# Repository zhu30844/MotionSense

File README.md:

# MotionSense

English | [简体中文](README_cn.md)

Last edited: 2026-11-27

> **Status.** To use MotionSense, take a
> [v1 release](https://github.com/zhu30844/MotionSense/releases) or the
> [`1.x` branch](https://github.com/zhu30844/MotionSense/tree/1.x). `main` is
> being reworked towards 2.0, and nothing on it is promised to work until 2.0
> is released.

Motion-triggered video recording for the Luckfox Pico Pro Max (Rockchip
RV1106; the Pico Ultra is planned for after 2.0). Records H.264 to HLS on
the SD card, serves a live view over WebRTC and a playback UI over HTTP, and
logs motion events to SQLite.

## What it is for

Originally written for a shared fridge — who took what. It may suit other
scenes of the same shape, static for hours with a few seconds of activity: a
dorm room, a store cupboard, a warehouse aisle, a basement.

- **Get through a whole day fast.** Idle stretches play back sped up, with no
  scrubbing back and forth.
- **See the moment at full speed.** Motion is recorded and played at the high
  rate.
- **Save storage.** Idle time is recorded at one frame per second, so a day of
  footage stays small.
- **See where the activity was.** Every switch to the high rate leaves a mark
  on the seek bar.

## Screenshots

Live view, with the OSD timestamp and the device status bar:

History: a calendar of the days with footage, coloured by how much motion each
day had:

Playback of one day. The red marks on the seek bar are the switches to the
high rate:

## Features

- **Adaptive frame rate.** Records at 1 fps while idle and about 30 fps while motion
  is detected. Thresholds, sensitivity and night mode are configurable.
- **HLS recording.** One `.ts` per keyframe by default, organised into
  date-based directories with a per-day event database and automatic cleanup
  when free space runs low.
- **Live view and playback.** Live H.264 over WebRTC, recordings
  browsable by date, plus a `/api/status` endpoint reporting uptime, memory,
  load, SoC temperature and the last day with footage.
- **OSD timestamp** burned into both the recording and the live stream.

## Requirements

- Luckfox Pico Pro Max, SPI NAND boot
- An SD card, **ext4**. It must not carry the `orphan_file` feature — the 5.10
  kernel cannot mount that read-write. See
  [docs/BUILD.md](docs/BUILD.md#the-sd-card).
- Enough card for the footage you want to keep. Below
  `storage.disk_free_min_mb`, 2 GB by default, the oldest day is deleted to
  make room; recording itself never stops.
- x86-64 Linux host

## Usage

1. **Flash the image.** Download the latest image and flash it to the onboard
   SPI NAND with the full one-click flash, not to the SD card. The Luckfox wiki
   covers how: [Getting Started](https://wiki.luckfox.com/Luckfox-Pico-RV1106/Getting-Started/Pico-Pro-Max/).
2. **Format the SD card as ext4.** On Windows, [DiskGenius](https://www.diskgenius.com/)
   can do it; on Linux, use the commands below.

   Check the version first with `mke2fs -V`. On 1.47 or later, run them as
   they are. Below 1.47 (Ubuntu 22.04 ships 1.46.5), drop `-O ^orphan_file`
   from step 4 of the commands, or it fails with `Invalid filesystem option
   set`; older versions never enable the feature anyway.

   ```bash
   # 1. Find the card first; do not pick the wrong disk
   lsblk -o NAME,SIZE,MODEL,MOUNTPOINTS

   # 2. Unmount any mounted partitions on the card
   sudo umount /dev/sdX?*

   # 3. Repartition: MBR, one partition across the whole card
   sudo parted -s /dev/sdX mklabel msdos mkpart primary ext4 1MiB 100%

   # 4. Format as ext4 without orphan_file
   sudo mkfs.ext4 -O ^orphan_file -m 0 -L MOTIONSENSE /dev/sdX1

   # 5. Check: orphan_file must not be in the output
   sudo dumpe2fs -h /dev/sdX1 | grep -i features
   ```

3. **Power up.** Insert the SD card and the camera, connect the network and
   power the board. It starts recording on boot with nothing to configure.
4. **Open the web page.** Browse to `http://<board IP>/` for the live view and
   playback. The address depends on how the board is connected:
   - **Ethernet to a router**: the board gets its address over DHCP. Find it in
     the router's device list, or with `adb shell ifconfig eth0`.
   - **USB to a computer**: the board's USB network interface is fixed at
     `172.32.0.93`, and the board gives the computer an address on the new
     interface that appears there. Open `http://172.32.0.93/`.
   - **Ethernet straight to a computer**: nothing hands out addresses, so both
     ends need one set by hand. See [Offline communication](https://wiki.luckfox.com/Luckfox-Pico-RV1106/Ethernet-Config/#1-offline-communication)
     on the Luckfox wiki.

## How it fits together

Two processes, split by what each language is good at:

- **`MotionSense`**, in C, owns the pipeline — ISP, encoder and IVS motion
  detection through Rockchip's rockit, writing HLS and the metadata databases
  to the card. Nothing sits between it and the hardware.
- **`motionsense-agent`**, in Go, owns the network — HTTP, the UI, the API. It
  never touches rockit, so **no cgo**: a static binary built with
  `CGO_ENABLED=0`, reading the databases through `modernc.org/sqlite` in pure
  Go. It serves on port 80 as root, 3000 otherwise.

They talk over a unix socket (`/tmp/motionsense-stream.sock`), which keeps the
split honest: the daemon can die without taking the web interface with it, and
the agent restarts without disturbing a recording.

Configuration is one `config.json` on the SD card. The daemon writes it with
the defaults on first boot and never overwrites it after that, so a blank card
still records. [docs/BUILD.md](docs/BUILD.md#configuration) lists the keys.

`S99motionsense` starts both; the vendor's `rkipc` app is not in the image. Each waits for the card to mount by itself, and is started again if it
exits; a recorder that stops storing frames resets the board through the
hardware watchdog. [docs/BUILD.md](docs/BUILD.md#supervision) has the
details. The script ships in the
image, so a flashed board records from first boot with nothing to install and
nothing to configure.

## Building

This is an application inside the Luckfox SDK, integrated the Rockchip SDK way
at `project/app/motionsense`. The SDK fork below carries the board
configuration, the device tree and the development environment; clone the
whole SDK:

**<https://github.com/zhu30844/luckfox-pico-sdk>**

```bash
git clone --recurse-submodules git@github.com:zhu30844/luckfox-pico-sdk.git
cd luckfox-pico-sdk
./build.sh lunch     # hardware "custom" -> MotionSense_Pro_Max
./build.sh
adb reboot loader                       # put the board in maskrom/loader mode
./rkflash.sh update
```

### Development container

The devcontainer is in the **SDK fork**, not in this repository — open
`luckfox-pico-sdk` in VS Code, not `MotionSense`. VS Code will offer *Reopen in
Container*; the image carries the cross toolchain, Go, and the build
dependencies, with `LF_SDK`, `LF_TOOLCHAIN` and `LF_SYSROOT` already set.

Editing this app means editing `project/app/motionsense` inside that workspace.
Building on the host works too — `./build.sh` puts the toolchain on `PATH`
itself — provided the SDK's build dependencies are installed.

[docs/BUILD.md](docs/BUILD.md) covers the build chain, the board configuration, the
on-device layout and what to check when something does not come up.
[docs/DEVNOTES.md](docs/DEVNOTES.md) covers working on the board: how to connect to it,
what to do when a link drops, and the bugs that present as something else.

## Known issues

- Switching between views raises the client count. Above about five clients
  the agent stops responding for a while.
- Motion has no hold window: the frame rate returns to 1 fps as soon as a
  still frame is reported. Events are typically under a second, so the end of
  an action can be recorded at the idle rate.
- Daylight saving is not honoured. Only the standard-time half of `/etc/TZ` is
  read, so a zone with DST is an hour out for half the year.

## Planned

See the [roadmap](docs/ROADMAP.md).

## Scope

A learning project. Not built, tested or reviewed as a security product, and
not suitable for one.

Concretely, on the image this repository produces:

- The HTTP interface has no authentication. Anyone who can reach port 80 can
  watch the live stream and every recording.
- The root password is the default, `luckfox`.
- Recordings and the metadata databases are unencrypted on the SD card.
- Nothing here has had a security review.

Use it only on a LAN you control. Do not expose it to the internet.

The author accepts no responsibility.

## Licence

MIT — see [LICENSE](LICENSE). [docs/THIRD-PARTY.md](docs/THIRD-PARTY.md) lists everything
in the tree that is not covered by it.

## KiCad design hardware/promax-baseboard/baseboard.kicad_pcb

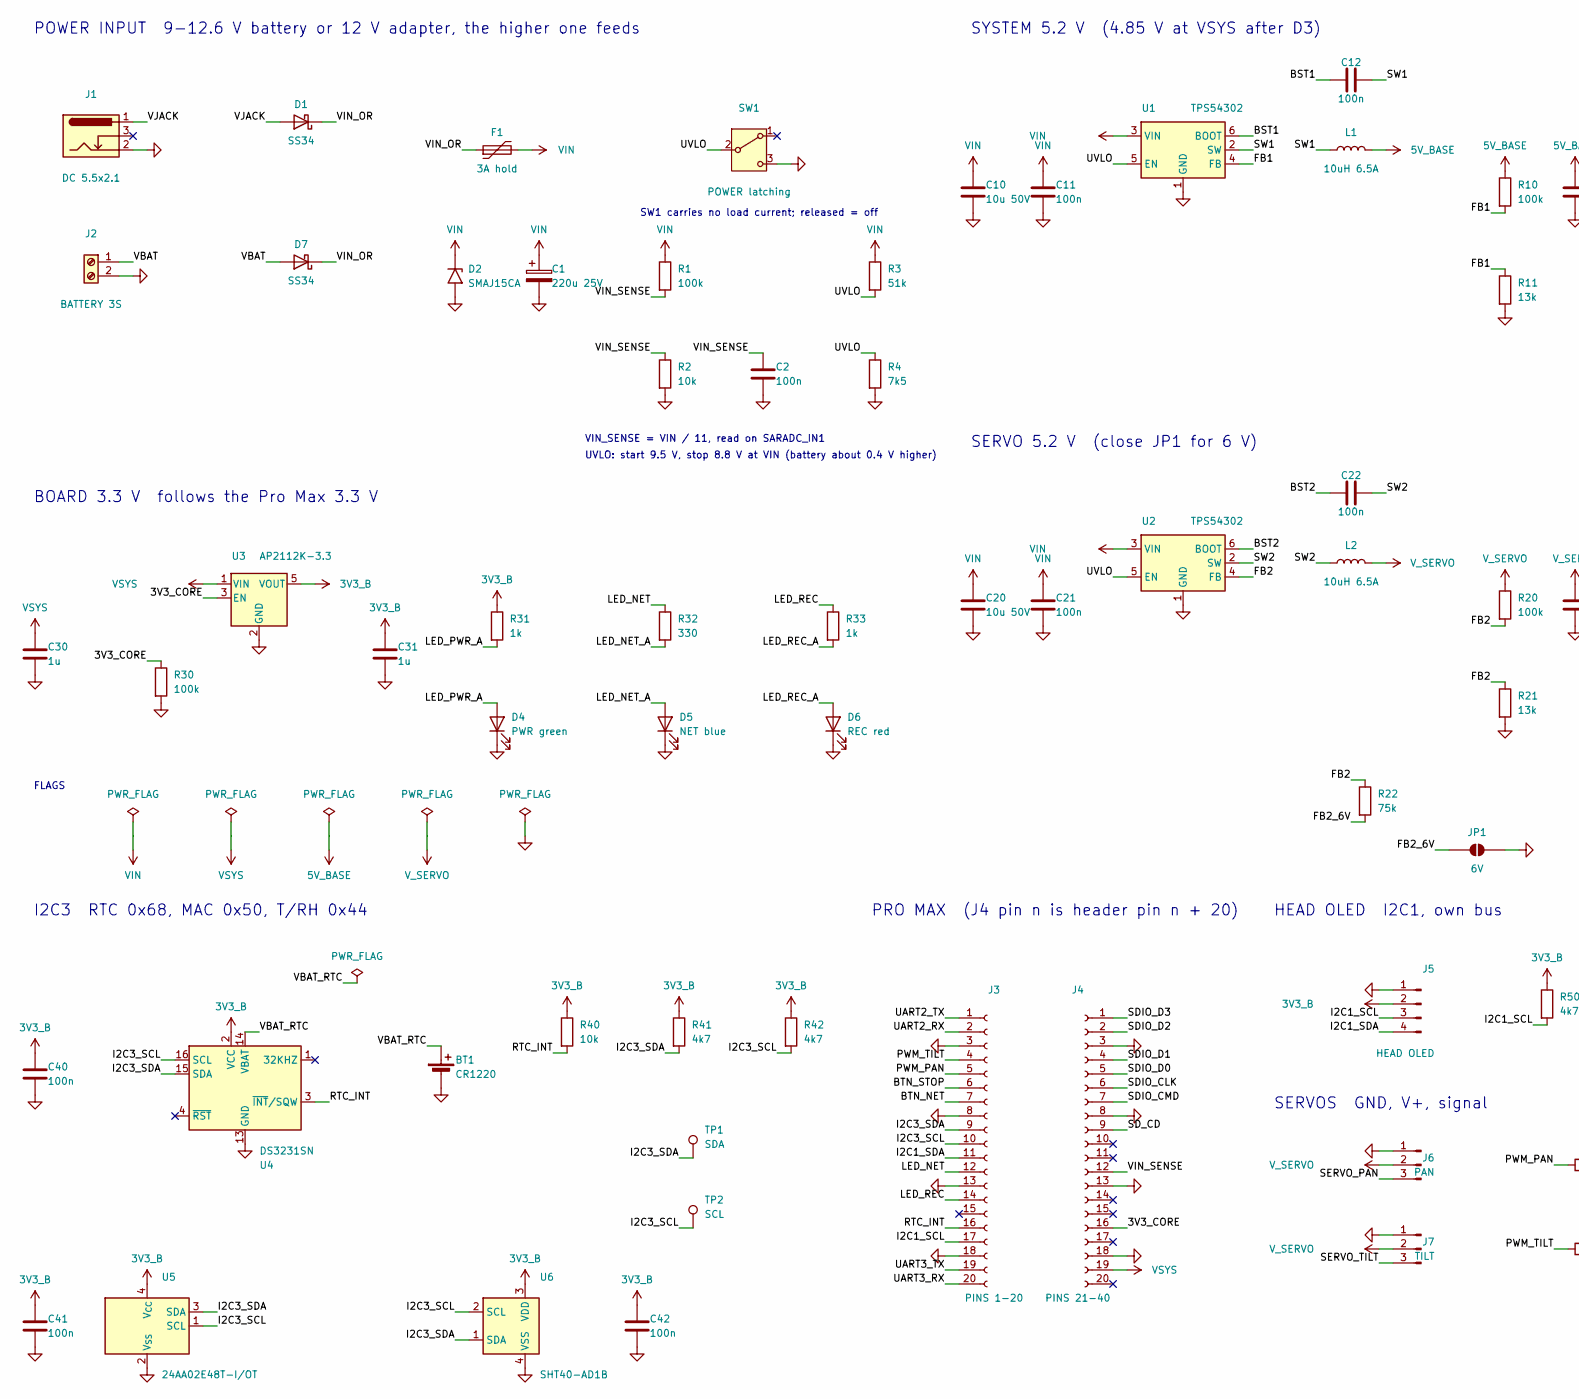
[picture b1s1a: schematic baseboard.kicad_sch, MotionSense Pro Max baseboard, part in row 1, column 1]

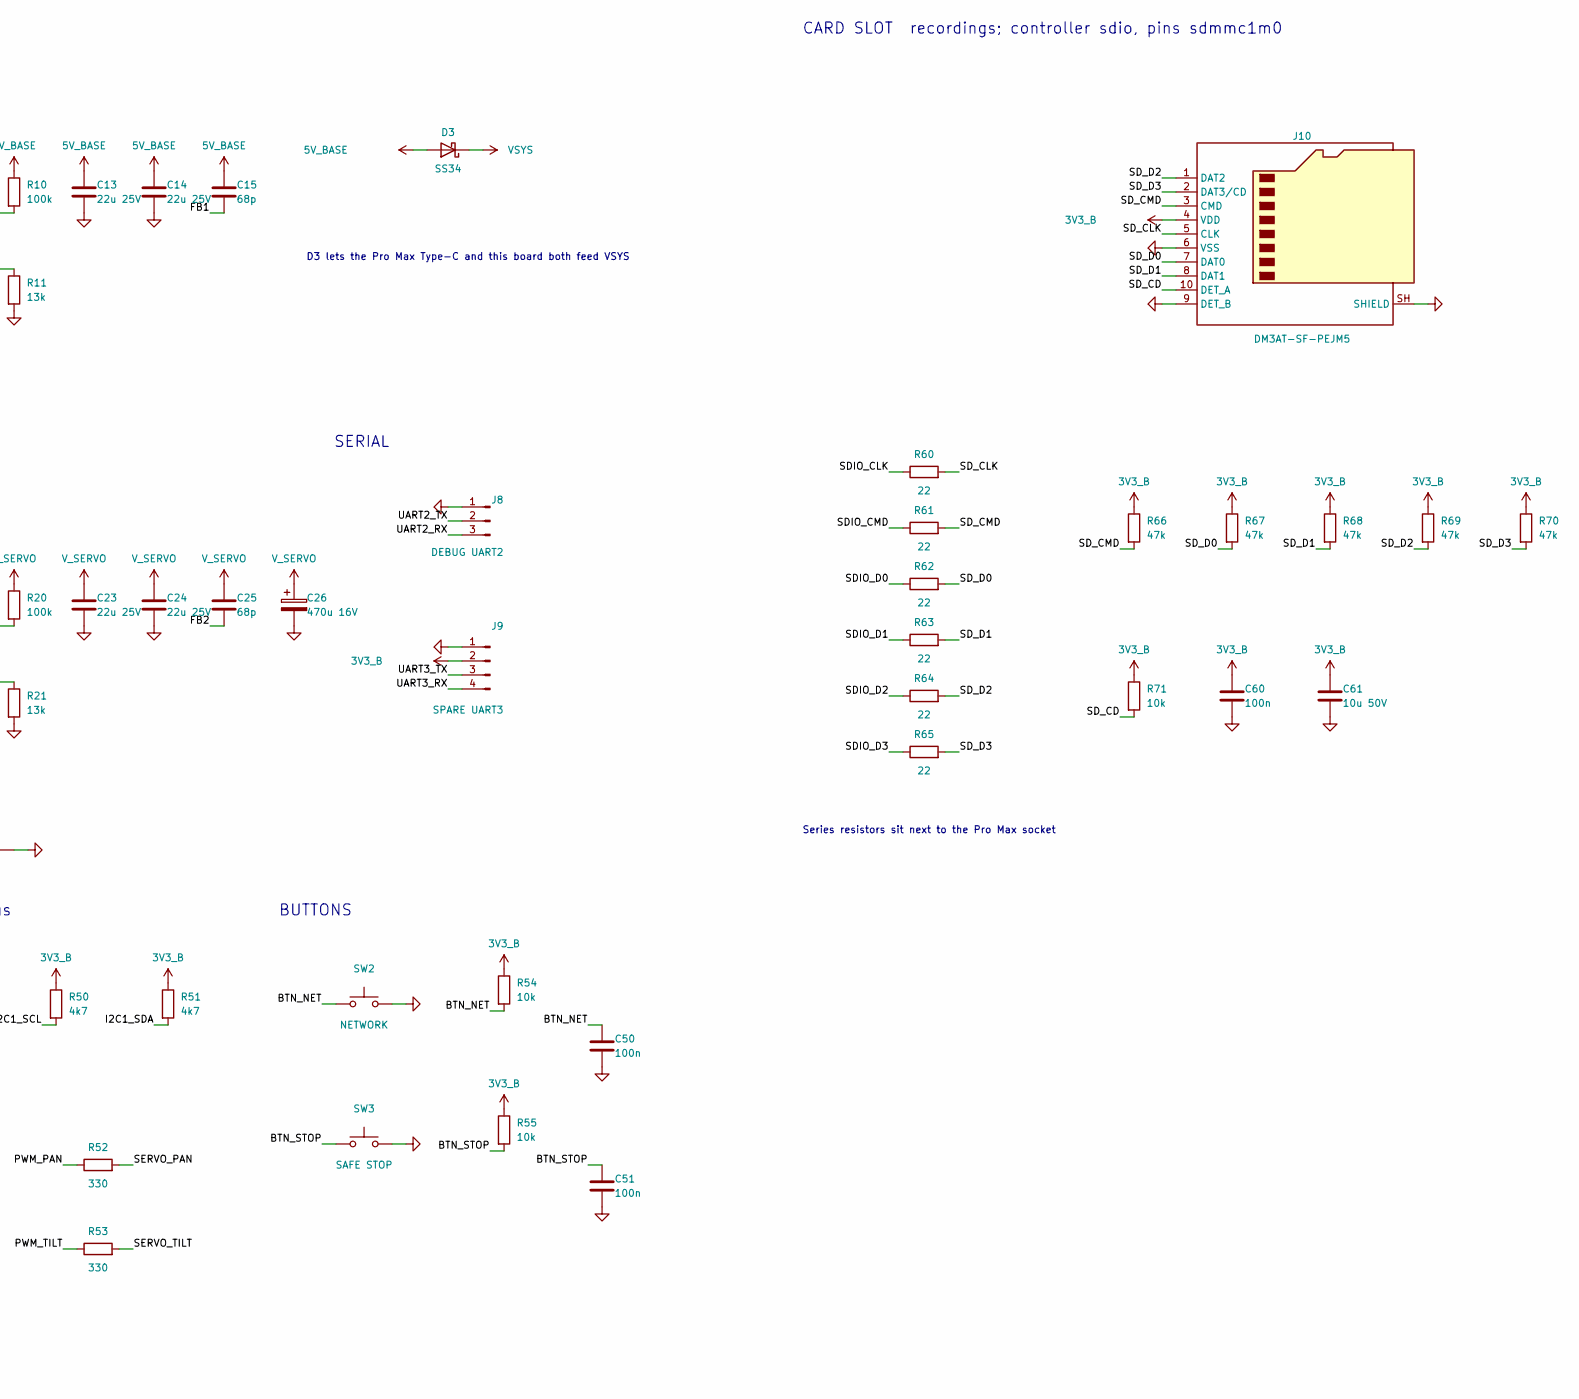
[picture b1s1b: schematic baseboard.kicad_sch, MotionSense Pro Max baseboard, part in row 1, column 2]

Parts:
BT1: CR1220; BAT-SMD_BS-12-B3AA011; LCSC C964723
C1: 220u 25V; CP_Elec_6.3x7.7; LCSC C2983317
C2, C11, C12, C21, C22, C40, C41, C42, C50, C51, C60: 100n; C_0805_2012Metric_Pad1.18x1.45mm_HandSolder; LCSC C49678
C10, C20, C61: 10u 50V; C_1206_3216Metric_Pad1.33x1.80mm_HandSolder; LCSC C13585
C13, C14, C23, C24: 22u 25V; C_1206_3216Metric_Pad1.33x1.80mm_HandSolder; LCSC C12891
C15, C25: 68p; C_0805_2012Metric_Pad1.18x1.45mm_HandSolder; LCSC C2171219
C26: 470u 16V; CP_Elec_6.3x7.7; LCSC C2977552
C30, C31: 1u; C_0805_2012Metric_Pad1.18x1.45mm_HandSolder; LCSC C28323
D1, D3, D7: SS34; D_SMA; LCSC C8678
D2: SMAJ15CA; D_SMA; LCSC C110044
D4: PWR green; LED_D3.0mm_Horizontal_O1.27mm_Z2.0mm; LCSC C181864
D5: NET blue; LED_D3.0mm_Horizontal_O1.27mm_Z2.0mm; LCSC C417350
D6: REC red; LED_D3.0mm_Horizontal_O1.27mm_Z2.0mm; LCSC C99771
F1: 3A hold; Fuse_1812_4532Metric_Pad1.30x3.40mm_HandSolder; LCSC C7500481
J1: DC 5.5x2.1; DC-IN-TH_DC-005-5.5-2.0; LCSC C16214
J2: BATTERY 3S; CONN-TH_P5.00_KF301-5.0-2P; LCSC C474881
J3: PINS 1-20; HDR-TH_20P-P2.54-V-F-2; LCSC C2905423
J4: PINS 21-40; HDR-TH_20P-P2.54-V-F-2; LCSC C2905423
J5: HEAD OLED; CONN-TH_B4B-XH-A-LF-SN; LCSC C144395
J6: PAN; PinHeader_1x03_P2.54mm_Vertical; LCSC C2937625
J7: TILT; PinHeader_1x03_P2.54mm_Vertical; LCSC C2937625
J8: DEBUG UART2; PinHeader_1x03_P2.54mm_Vertical; LCSC C2937625
J9: SPARE UART3; PinHeader_1x04_P2.54mm_Vertical; LCSC C2691448
J10: DM3AT-SF-PEJM5; microSD_HC_Hirose_DM3AT-SF-PEJM5; LCSC C114218
JP1: 6V; SolderJumper-2_P1.3mm_Open_RoundedPad1.0x1.5mm
L1, L2: 10uH 6.5A; IND-SMD_L7.5-W6.6_GSM0650; LCSC C51933843
R1, R10, R20, R30: 100k; R_0805_2012Metric_Pad1.20x1.40mm_HandSolder; LCSC C149504
R2, R40, R54, R55, R71: 10k; R_0805_2012Metric_Pad1.20x1.40mm_HandSolder; LCSC C17414
R3: 51k; R_0805_2012Metric_Pad1.20x1.40mm_HandSolder; LCSC C17737
R4: 7k5; R_0805_2012Metric_Pad1.20x1.40mm_HandSolder; LCSC C17807
R11, R21: 13k; R_0805_2012Metric_Pad1.20x1.40mm_HandSolder; LCSC C17455
R22: 75k; R_0805_2012Metric_Pad1.20x1.40mm_HandSolder; LCSC C17819
R31, R33: 1k; R_0805_2012Metric_Pad1.20x1.40mm_HandSolder; LCSC C17513
R32, R52, R53: 330; R_0805_2012Metric_Pad1.20x1.40mm_HandSolder; LCSC C17630
R41, R42, R50, R51: 4k7; R_0805_2012Metric_Pad1.20x1.40mm_HandSolder; LCSC C17673
R60, R61, R62, R63, R64, R65: 22; R_0805_2012Metric_Pad1.20x1.40mm_HandSolder; LCSC C17561
R66, R67, R68, R69, R70: 47k; R_0805_2012Metric_Pad1.20x1.40mm_HandSolder; LCSC C17713
SW1: POWER latching; SW-TH_6P-8.5-8.5-ZS; LCSC C5379895
SW2: NETWORK; SW-TH_4P-L6.0-W6.0-P4.50-LS6.5; LCSC C2837515
SW3: SAFE STOP; SW-TH_4P-L6.0-W6.0-P4.50-LS6.5; LCSC C2837515
TP1: SDA; TestPoint_Pad_D1.5mm
TP2: SCL; TestPoint_Pad_D1.5mm
U1, U2: TPS54302; SOT-23-6; LCSC C311983
U3: AP2112K-3.3; SOT-23-5; LCSC C51118
U4: DS3231SN; SOIC-16W_7.5x10.3mm_P1.27mm; LCSC C9866
U5: 24AA02E48T-I/OT; SOT-23-5; LCSC C38987
U6: SHT40-AD1B; Sensirion_DFN-4_1.5x1.5mm_P0.8mm_SHT4x_NoCentralPad; LCSC C2909890

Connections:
3V3_B: C31.1, C40.1, C41.1, C42.1, C60.1, C61.1, J5.2, J9.2, J10.4 (VDD), R31.1, R40.1, R41.1, R42.1, R50.1, R51.1, R54.1, R55.1, R66.1, R67.1, R68.1, R69.1, R70.1, R71.1, U3.5 (VOUT), U4.2 (VCC), U5.4 (V_{CC}), U6.3 (VDD)
5V_BASE: C13.1, C14.1, C15.1, D3.2 (A), L1.2, R10.1
/3V3_CORE: J4.16, R30.1, U3.3 (EN)
/BST1: C12.1, U1.6 (BOOT)
/BST2: C22.1, U2.6 (BOOT)
/BTN_NET: C50.1, J3.7, R54.2, SW2.1
/BTN_STOP: C51.1, J3.6, R55.2, SW3.1
/FB1: C15.2, R10.2, R11.1, U1.4 (FB)
/FB2: C25.2, R20.2, R21.1, R22.1, U2.4 (FB)
/FB2_6V: JP1.1 (A), R22.2
/I2C1_SCL: J3.17, J5.3, R50.2
/I2C1_SDA: J3.11, J5.4, R51.2
/I2C3_SCL: J3.10, R42.2, TP2.1, U4.16 (SCL), U5.1 (SCL), U6.2 (SCL)
/I2C3_SDA: J3.9, R41.2, TP1.1, U4.15 (SDA), U5.3 (SDA), U6.1 (SDA)
/LED_NET: J3.12, R32.1
/LED_NET_A: D5.2 (A), R32.2
/LED_PWR_A: D4.2 (A), R31.2
/LED_REC: J3.14, R33.1
/LED_REC_A: D6.2 (A), R33.2
/PWM_PAN: J3.5, R52.1
/PWM_TILT: J3.4, R53.1
/RTC_INT: J3.16, R40.2, U4.3 (~INT/SQW)
/SDIO_CLK: J4.6, R60.1
/SDIO_CMD: J4.7, R61.1
/SDIO_D0: J4.5, R62.1
/SDIO_D1: J4.4, R63.1
/SDIO_D2: J4.2, R64.1
/SDIO_D3: J4.1, R65.1
/SD_CD: J4.9, J10.10 (DET_A), R71.2
/SD_CLK: J10.5 (CLK), R60.2
/SD_CMD: J10.3 (CMD), R61.2, R66.2
/SD_D0: J10.7 (DAT0), R62.2, R67.2
/SD_D1: J10.8 (DAT1), R63.2, R68.2
/SD_D2: J10.1 (DAT2), R64.2, R69.2
/SD_D3: J10.2 (DAT3/CD), R65.2, R70.2
/SERVO_PAN: J6.3, R52.2
/SERVO_TILT: J7.3, R53.2
/SW1: C12.2, L1.1, U1.2 (SW)
/SW2: C22.2, L2.1, U2.2 (SW)
/UART2_RX: J3.2, J8.3
/UART2_TX: J3.1, J8.2
/UART3_RX: J3.20, J9.4
/UART3_TX: J3.19, J9.3
/UVLO: R3.2, R4.1, SW1.2 (B), U1.5 (EN), U2.5 (EN)
/VBAT: D7.2 (A), J2.1
/VBAT_RTC: BT1.1 (+), U4.14 (VBAT)
/VIN_OR: D1.1 (K), D7.1 (K), F1.1
/VIN_SENSE: C2.1, J4.12, R1.2, R2.1
/VJACK: D1.2 (A), J1.1
GND: BT1.2 (-), C1.2, C2.2, C10.2, C11.2, C13.2, C14.2, C20.2, C21.2, C23.2, C24.2, C26.2, C30.2, C31.2, C40.2, C41.2, C42.2, C50.2, C51.2, C60.2, C61.2, D2.2 (A2), D4.1 (K), D5.1 (K), D6.1 (K), J1.2, J2.2, J3.3, J3.8, J3.13, J3.18, J4.3, J4.8, J4.13, J4.18, J5.1, J6.1, J7.1, J8.1, J9.1, J10.6 (VSS), J10.9 (DET_B), J10.SH (SHIELD), JP1.2 (B), R2.2, R4.2, R11.2, R21.2, R30.2, SW1.3 (C), SW2.2, SW3.2, U1.1 (GND), U2.1 (GND), U3.2 (GND), U4.5 (GND), U4.6 (GND), U4.7 (GND), U4.8 (GND), U4.9 (GND), U4.10 (GND), U4.11 (GND), U4.12 (GND), U4.13 (GND), U5.2 (V_{SS}), U6.4 (VSS)
VIN: C1.1, C10.1, C11.1, C20.1, C21.1, D2.1 (A1), F1.2, R1.1, R3.1, U1.3 (VIN), U2.3 (VIN)
VSYS: C30.1, D3.1 (K), J4.19, U3.1 (VIN)
V_SERVO: C23.1, C24.1, C25.1, C26.1, J6.2, J7.2, L2.2, R20.1

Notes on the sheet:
POWER INPUT 9-12.6 V battery or 12 V adapter, the higher one feeds
SW1 carries no load current; released = off
VIN_SENSE = VIN / 11, read on SARADC_IN1
UVLO: start 9.5 V, stop 8.8 V at VIN (battery about 0.4 V higher)
SYSTEM 5.2 V (4.85 V at VSYS after D3)
D3 lets the Pro Max Type-C and this board both feed VSYS
SERVO 5.2 V (close JP1 for 6 V)
BOARD 3.3 V follows the Pro Max 3.3 V
PRO MAX (J4 pin n is header pin n + 20)
I2C3 RTC 0x68, MAC 0x50, T/RH 0x44
HEAD OLED I2C1, own bus
SERVOS GND, V+, signal
SERIAL
BUTTONS
CARD SLOT recordings; controller sdio, pins sdmmc1m0
Series resistors sit next to the Pro Max socket
FLAGS

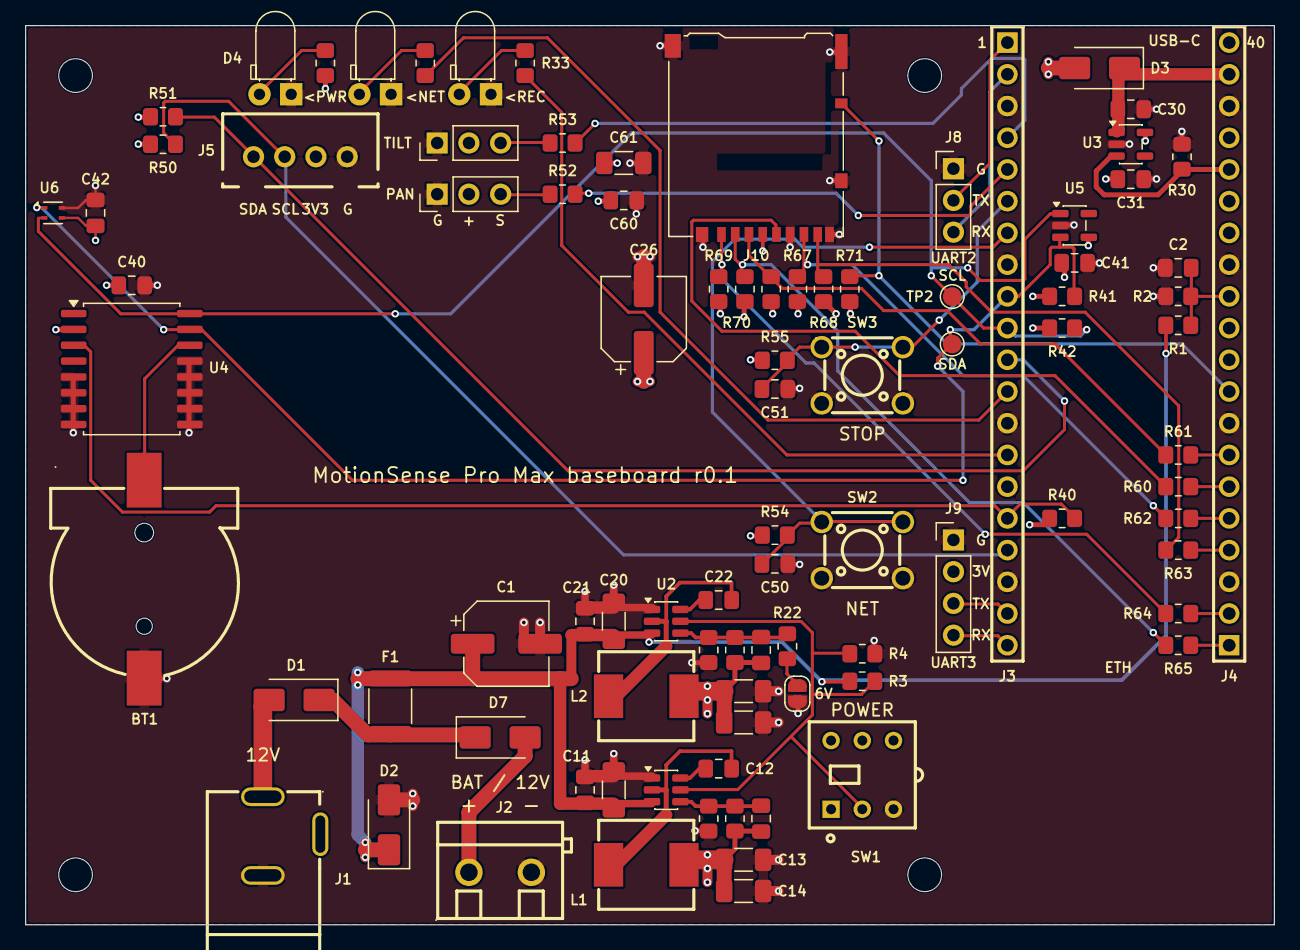
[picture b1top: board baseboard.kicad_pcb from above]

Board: 4 copper layers, 100.0 x 72.0 mm, 95 parts (0 on the bottom side), 53 nets.

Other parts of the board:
H1, H2, H3, H4: MountingHole_2.7mm_M2.5

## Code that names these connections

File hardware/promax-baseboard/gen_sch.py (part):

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
# ---- Pan-tilt head, servos, serial ports ------------------------------------
text("HEAD OLED  I2C1, own bus", 245, 185)
place("Connector:Conn_01x04_Pin", "J5", "HEAD OLED", 271.78, 200.66, {"1": GND, "2": "3V3_B", "3": "I2C1_SCL", "4": "I2C1_SDA"},
      mirror=True, fp="baseboard:CONN-TH_B4B-XH-A-LF-SN", refat=(274.3, 194.3, "left"), valat=(274.3, 209.6, "left"))
R("R50", "4k7", 294.64, 200.66, "3V3_B", "I2C1_SCL")
R("R51", "4k7", 314.96, 200.66, "3V3_B", "I2C1_SDA")
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text("SERVOS  GND, V+, signal", 245, 220)
for i, name in enumerate(["PAN", "TILT"]):
    y = 229.87 + i * 15.24
    place("Connector:Conn_01x03_Pin", "J%d" % (6 + i), name, 271.78, y, {"1": GND, "2": "V_SERVO", "3": "SERVO_" + name},
          mirror=True, fp=HDR % 3, refat=(274.3, y - 1.3, "left"), valat=(274.3, y + 1.3, "left"))
    horiz("Device:R", "R%d" % (52 + i), "330", 302.26, y, "PWM_" + name, "SERVO_" + name, R0805)

text("SERIAL", 345, 100)
place("Connector:Conn_01x03_Pin", "J8", "DEBUG UART2", 373.38, 113.03, {"1": GND, "2": "UART2_TX", "3": "UART2_RX"},
      mirror=True, fp=HDR % 3, refat=(375.9, 109.2, "left"), valat=(375.9, 118.7, "left"))
place("Connector:Conn_01x04_Pin", "J9", "SPARE UART3", 373.38, 138.43, {"1": GND, "2": "3V3_B", "3": "UART3_TX", "4": "UART3_RX"},
      mirror=True, fp=HDR % 4, refat=(375.9, 132.1, "left"), valat=(375.9, 147.3, "left"))

text("BUTTONS", 335, 185)
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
